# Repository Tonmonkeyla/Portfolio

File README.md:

# Engineering Portfolio

Electrical Engineering student at the University of Canterbury with an interest in embedded systems, RF, aerospace, and power electronics.

## Projects

### GNSS Navigator (STM32 + OpenStreetMaps)
Low-power embedded navigation system built around an STM32 MCU.

- Custom four-layer PCB integrating GNSS, IMU and magnetometer
- C firmware for waypoint navigation and map rendering
- Python tools to compress OpenStreetMap data into binary tiles suitable for MCU storage
- SD card tile streaming based on live NMEA position
- Future revision will incorporate a low-power e-paper display

**Technologies:** STM32, C, Python, KiCad, OpenStreetMaps

---

### Monitor Rotator (ESP32 + BLE)
Wireless monitor orientation sensor powered directly from an HDMI connection.

- Designed a four-layer ESP32 PCB with inertial sensing and BLE
- Developed firmware using ESP-IDF
- Desktop Python application receives orientation data and rotates the display automatically
- Characterised and tuned the integrated 2.4 GHz PCB antenna using a VNA

**Technologies:** ESP32, ESP-IDF, BLE, Python, RF Design

---

### Portable Trailer Light Tester
Battery-powered trailer light tester for automotive diagnostics.

- High-current synchronous buck converter
- Automated lighting test sequences
- Designed for portable operation from an internal battery
- Custom PCB and embedded control firmware

**Technologies:** Power Electronics, Embedded C, KiCad

---

### High-Efficiency LED Array
Custom circular LED lighting module.

- Python-generated PCB layout for uniform LED spacing
- Constant-current buck driver achieving approximately 93% estimated efficiency
- Designed for future integration into IoT lighting systems

**Technologies:** Python, PCB Design, Power Electronics

---

### Artix-7 System-on-Module *(In Progress)*
High-performance FPGA module based on a Xilinx Artix-7.

- Eight-rail power architecture with sequencing
- DDR3 routing and length matching
- Python routing optimisation tools
- High-speed PCB layout

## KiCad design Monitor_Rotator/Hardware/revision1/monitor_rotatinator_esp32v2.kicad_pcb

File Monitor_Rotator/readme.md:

The main idea behind this project was that the internet is becoming increasingly "vertical"; many apps/websites are designed primarily for mobile usage, with desktops being a faint afterthought. 
However, many monitors can be physically rotated, vertically<->horizontally, easily and quickly. The issue lies with manually setting the orientation of the monitor in the operating system; ie. in windows this can only be changed in the display settings. 
Monitors do not "know" what orientation they are in. They simply display images, and do not have the hardware to detect orientation.
A solution to this is to couple an accelerometer to the orientation of the monitor. The easy, and boring, way to do this is to simply attach an externally powered accelerometer board to the monitor (tape).
However this gets messy fast, the power and data cables get tangled with the existing monitor connections, making it a temporary solution at best. 
Powering the accelerometer board directly from the monitor and transmitting the accelerometer data back to the host PC wirelessly solves this, with exactly 0 additional cables.

The complex problem is receiving power from the monitor. While some monitors have USB passthrough and therefore a nice 5V DC supply, most do not. In fact, almost none of the connectors on a standard monitor have any power supply whatsoever, the exception being 500mA DP_PWR 3.3V on DisplayPort inputs.
Unfortunately, most monitors have a single DisplayPort, which is often the main display input. This leaves exactly 0 conventional, viable power supplies. 

HDMI uses a lot of power to receive signals from the host PC (up to ~130 mW). This is largely due to transceiver TMDS terminations being present on the input side, which are directly tied to the exposed connector transceiver pairs. These terminations are implemented as 50 ohm parallel terminations to aVCC, a 3.3v source. A logical zero from the host PC sinks around 10mA of current per termination resistor, which for a typical data pattern (~50% low) is substantial across the 8 terminations available. This effectively means we can sink 5mA*8=~40mA of 3.05V across the 50 ohm terminations, while technically remaining within HDMI design specification. 

This leads to another challenge- how do you consistently sink no greater than 5mA per termination while maximising the available power budget. Connecting the terminations directly to a device side 3.3V net is clearly a bad idea; RF MCUs can draw up to 200mA while transmitting, and even if that were possible within the voltage drop of the terminations it would fry the HDMI aVCC supply instantly. And it isn't possible because it would result in a voltage drop brownout+the catastrophic overcurrent of the HDMI circuit. Initially, my idea was to use a discrete linear current regulator- tie all terminations together through a shunt resistor, V=IR, hold I at 40mA etc. This would use a low VGS PFET in conjunction with a current sense OP-amp to limit the input current to 40mA through to a large capacitor or supercapacitor. Given a (very) low average current draw of the MCU, the voltage of the capacitor net would eventually charge to ~3.3V, which could then be regulated down to an MCU operating voltage of 1.8V or 3V.

The version 2 hardware instead uses a buck converter with op-amp regulated voltage foldback. 6 of the available 8 terminations are used as power terminations, with variable voltage across the termination according to current draw. The remaining 2 are used as reference voltages with minimal current draw; and remain at ~3.3v. The differential voltage between the "reference" and "power" nets is used by the differential op amp to sense average current through the power terminations; and raise the feedback voltage of the buck converter high when input current is exceeded. This effectively uses the 50 ohm terminations themselves as current sense resistors. This current foldback protects the HDMI transceivers from any possible damage.

The power net voltage can approach the reference/VDD "3.3v", so a relatively specialized over the rails OP amp (MCP6021) was required. It was initially designed for the LMV321, however as it turns out the LMV321 does not have rail to rail inputs, as most modern OP-amps have. Additionally the LMV321 has a nasty characteristic when the input differential drops below specification, where the output inverts, effectively dropping the output voltage to the negative rail. As you can imagine buck regulator feedback loops do not tolerate this.

This current regulation feeds into a large (5.7 mF) electrolytic polymer capacitor, which over 100s of mS charges to slightly less than 3.3v. This capacitor net is then regulated to 3.3v exactly using a low quiescent, ultra low input voltage boost converter (TPS61299). This provides stable and low noise power for the MCU, accelerometer, and associated RF circuitry. 

Probing the assembled version 2 revealed that current through the terminations could spike outside of specifications:
A. During startup, when there is significant inrush current into the VIN bulk capacitors of the buck converter.
B. During current spikes on the load side.

The solution to this was to add an additional linear current regulator immediately after the termination nets on the device side. This uses one op-amp unit of a two unit device to control a PFET gate. When the device side termination voltage drops below a set threshold the PFET gate is pulled high to maintain the set current limit, with a very fast response time.

The red trace shows current through R18 into a 2x47uF input bank during startup. Current peaks at 60 mA for a few nanoseconds, before being arrested and maintained at 45 mA until the capacitors are charged and inrush current drops, at which point the switching circuit takes over current regulation. Without the linear regulator it would effectively be 3.3V->50 ohms->ground at startup, drawing ~60 mA (per termination) so 360 mA total through the HDMI transceiver, which would probably fry it.

The "hard" linear current limit and "soft" switching current limit are both user adjustable through potentiometers on the finished board:

This allows for differences in voltage drop through the summing diodes and op-amp differences to be accounted for experimentally.

The MCU chosen was the ESP32C3. In hindsight, this was a poor decision as the BLE power consumption is diminished by sharing circuitry with WIFI. During transmission this can spike to >300 mA at 3.3v, and even in the lowest power, connection maintaining, state still uses ~20 mA on average. This stresses the power budget at best and causes intermittent brownouts when transmissions are not optimized. Eg. to even establish a BLE connection the buffering capacitance needed to be doubled to 11.4 mF. The in-progress version 3 uses a NRF54 series MCU, with less than a tenth of the power consumption, at 1v8.

The version 2 uses a 3216 chip antenna for BLE/WIFI, while the version 2 rev 2 uses a TI AN043 inverted F pcb antenna. 

Surprisingly, both held a stable connection within operating parameters (ie. BLE, within 5 meters) without any tuning, fitting only a 0 ohm as the series element of the PI network. However, the performance was subpar beyond that. As modern RF socs generally adjust the transmission power according to RSSI, it was desirable to increase the antenna efficiency to reduce the power consumption of each packet. 

This required assaying the antenna(s) with a VNA. This was challenging as an RF test port was neglected in both designs. The first attempt was simply soldering a RG316 pigtail to the feedpoint of the antenna:

Unsurprisingly this didn't give a good measurement; with the resonant frequency of the antenna measuring ~1.9 GHz showing that it was significantly detuned by the test fixture:

For the second attempt I instead removed some solder mask, exposing the ground plane into a U.FL-like footprint, then soldered an IPEX-1 connector to it:

This allowed the coaxial shield to be rotated away from the radiating area:

And gave slightly more believable S11, with resonance now measuring around 2.1 GHz:

Which is likely still altered by the large U.FL connector directly adjacent to the radiating area.

Interestingly, rotating the U.FL connector back to parallel with the radiating area detuned the antenna similarly to the pigtail, with S11 resonance dropping back to 1.9 GHz.

Despite the measurements likely still being altered by the U.FL connector, the Smith Chart of the configurating with the coaxial rotated away from the radiating area was used to determine matching component values.

Which, if naively believed, shows that the antenna is very poorly matched with an impedance of 40.7-76.6j ohms at 2.4GHz, and 16.4-35.8j at 2.44Ghz. This suggests a very preliminary matching network on the order of 2-5 nH of series inductance and 1-2 pF of shunt capacitance.

A better takeaway is to always include RF test feedpoints that are sufficiently isolated from the antenna, like a jumper connected U.FL connector (with minimal routed stub) at the opposite end of the transmission line.

### Version 3
Uses STM32WB05 with orders of magnitude lower BLE power consumption over ESP32C3. Larger power budget enables far more robust resistive power supply:

Every TMDS string is individually ORed into a >40F LIC hybrid supercapacitor operating between 3v3 and 2v5, each string is in series with a 100 ohm resistor, current through each termination physically cannot exceed 6 mA, albeit with acceptable resistive losses. 
Individual current limiting resistors makes device compatible with larger range of monitors. Not all monitors power on all transceiver pairs at all times, and some completely power off all transceivers until HPD or source 5V is asserted. Testing shows that when 5V or HPD is asserted a significant subset of monitors raise all transceiver pairs, while some only raise the CLK pair. The power scheme passively handles these cases, and can assert 5V lines through a low quiescent boost 5v net. Low supercapacitor leakage and very low total device current draw (~40 uA) means that the device should be able to operate for ~weeks without any external power at all.   

Dedicated antenna test port/alternate feed through IPX-1 footprint, placed away from antenna on counterbalance side, away from main radiating area. Could use more clearance.

Replaced LTC3406 with better suited TPS62743/RT5707/many clones BGA-8 footprint, quiescent current 350 nA with optimal efficiency in the 10s uA range. Fabrication soon.

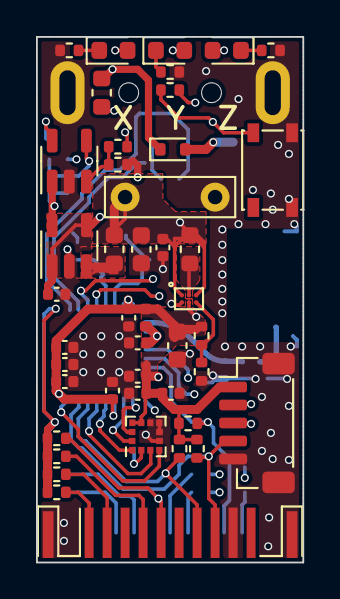
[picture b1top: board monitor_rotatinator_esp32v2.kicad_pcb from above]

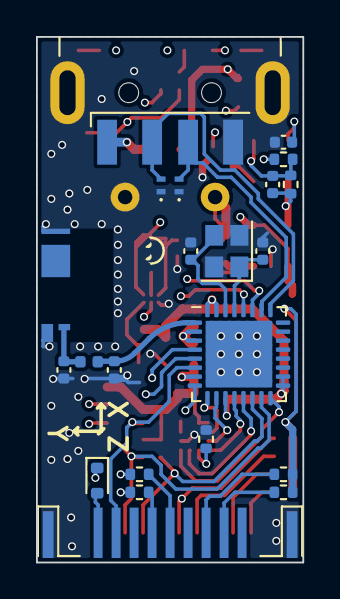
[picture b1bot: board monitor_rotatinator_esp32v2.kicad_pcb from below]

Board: 4 copper layers, 14.8 x 29.2 mm, 65 parts (21 on the bottom side), 46 nets.

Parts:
AE1: Antenna_Chip; RFECA3216060A1T
C1, C10, C20: 4.7uF; C_0402_1005Metric
C3: C_Polarized; C_Rect_L7.0mm_W2.0mm_P5.00mm
C5: 2.2uF; C_0402_1005Metric
C6, C22: 10uF; C_0603_1608Metric
C7, C8: 22pF; C_0402_1005Metric
C9, C11, C13, C16, C17, C18, C19: 100nF; C_0402_1005Metric
C12, C14: TBD; C_0402_1005Metric
C15: 10uF; C_0402_1005Metric
C21: 470p; C_0402_1005Metric
D3, D4, D9: LED; LED_0603_1608Metric
D5, D8: D_Small; D_SOD-523
D6, D7: D_TVS; Texas_DPY0002A_0.6x1mm_P0.65mm
F1: Fuse; Fuse_0603_1608Metric
J1: USB_A; USB_A_CNCTech_1001-011-01101_Horizontal
J2: HDMI_A_1.4; HDMI_A_Contact_Technology_HDMI-19APL2_Horizontal
J3: Conn_01x05_MountingPin; JST_SH_BM05B-SRSS-TB_1x05-1MP_P1.00mm_Vertical
L1: 1uH; L_0603_1608Metric
L2: 2.0nH; L_0402_1005Metric
L3: 0R; L_0402_1005Metric
L4: 2.2uH; L_0603_1608Metric
R5, R6, R16, R17, R18, R19, R20, R21, R22, R23: R_Small; R_0402_1005Metric
R7: DNF; R_0402_1005Metric
R8: 0; R_0402_1005Metric
R9: 100k; R_0402_1005Metric
R10, R14, R26, R29: 10k; R_0402_1005Metric
R11, R12, R13: 330R; R_0402_1005Metric
R27: 6.8k; R_0402_1005Metric
R28: 20k; R_0402_1005Metric
SW1: SW_SPST; SW_SPST_PTS810
U1: LTC3406AES5; TSOT-23-5
U2: WLCSP-6_1.4x1.0mm_P0.4mm
U4: ESP32-C3FH4; QFN-32-1EP_5x5mm_P0.5mm_EP3.7x3.7mm
U5: LIS2DE12; LGA-12_2x2mm_P0.5mm
U6: TSV911xxLx; SOT-23-5
Y1: 40MHz; Crystal_SMD_2520-4Pin_2.5x2.0mm

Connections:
+3V3: C6.1, C9.1, C10.1, C13.1, C15.1, C16.1, C17.1, C18.1, C19.1, J3.1, L2.2, R5.1, R6.1, R7.1, R10.1, R14.1, U2.B2 (VOUT), U4.7 (CHIP_EN), U4.11 (VDD3P3_RTC), U4.17 (VDD3P3_CPU), U4.18 (VDD_SPI), U4.31 (VDDA), U4.32 (VDDA__1), U5.9 (Vdd), U5.10 (Vdd_IO)
ACC_INT1: U4.10 (MTDI), U5.12 (INT1)
ACC_INT2: U4.9 (MTMS), U5.11 (INT2)
ACC_MISO: U4.13 (MTDO), U5.3 (SA0/SDO)
ACC_MOSI: U4.16 (GPIO10), U5.4 (SDA/SDI)
ACC_SCK: U4.12 (MTCK), U5.1 (SCL/SPC)
A_D+: D6.2 (A2), J1.3 (D+), U4.26 (GPIO19)
A_D-: D7.2 (A2), J1.2 (D-), U4.25 (GPIO18)
A_VBUS: D5.2 (A), J1.1 (VBUS)
CK+: J2.10 (CK+), R23.2
CK-: J2.12 (CK-), R22.2
Cap_V+: C3.1, C5.1, C22.1, L1.1, L4.2, U2.A1 (VIN), U2.C1 (EN), U4.4 (XTAL_32K_P)
D0+: J2.7 (D0+), R19.2
D0-: J2.9 (D0-), R18.2, R27.1
D1+: J2.4 (D1+), R20.2
D1-: J2.6 (D1-), R21.2
D2+: J2.1 (D2+), R16.2
D2-: J2.3 (D2-), R17.2
GND: AE1.2 (PCB_Trace), C1.2, C3.2, C5.2, C6.2, C7.1, C8.2, C9.2, C10.2, C11.2, C12.2, C13.2, C14.2, C15.2, C16.2, C17.2, C18.2, C19.2, C20.2, C22.2, D6.1 (A1), D7.1 (A1), J1.4 (GND), J1.5 (Shield), J2.17 (GND), J2.SH, J3.5, J3.MP (MountPin), R8.2, R9.2, R11.2, R12.2, R13.2, R28.2, SW1.1 (A), U1.2 (GND), U2.A2 (GND), U4.33 (GND), U5.5 (RES), U5.6 (GND), U5.7 (GND), U5.8 (GND), U6.2 (V-), Y1.2, Y1.4
GPIO2: J2.16 (SDA), R6.2, U4.6 (GPIO2)
GPIO8: J2.13 (CEC), R5.2, U4.14 (GPIO8)
GPIO9: J2.15 (SCL), J3.4, R10.2, U4.15 (GPIO9)
unnamed: AE1.1 (FEED), C14.1, L3.2
unnamed: D3.1 (K), R11.1
unnamed: D4.1 (K), R12.1
unnamed: D8.2 (A), J2.18 (+5V)
unnamed: D9.1 (K), R13.1
unnamed: R23.1, R26.2
unnamed: C20.1, F1.1, U1.1 (RUN), U1.4 (VIN)
unnamed: L4.1, U1.3 (SW)
unnamed: C21.2, R29.2, U1.5 (VOUT), U6.1
unnamed: L1.2, U2.B1 (SW)
unnamed: R7.2, R8.1, U2.C2 (VSEL)
unnamed: C12.1, L3.1, U4.1 (LNA_IN)
unnamed: C11.1, L2.1, U4.2 (VDD3P3), U4.3 (VDD3P3__1)
unnamed: C7.2, U4.29 (XTAL_N), Y1.1
unnamed: C8.1, U4.30 (XTAL_P), Y1.3
unnamed: R9.1, U5.2 (~CS)
unnamed: R26.1, R28.1, U6.3 (+)
unnamed: C21.1, R27.2, R29.1, U6.4 (-)
unnamed: C1.1, R22.1, U6.5 (V+)
RXD: D3.2 (A), J3.3, U4.27 (U0RXD)
TXD: D4.2 (A), J3.2, U4.28 (U0TXD)
User_LED3: D9.2 (A), U4.8 (GPIO3)
User_SW1: R14.2, SW1.2 (B), U4.5 (XTAL_32K_N)
VBUS: D5.1 (K), D8.1 (K), F1.2, R16.1, R17.1, R18.1, R19.1, R20.1, R21.1

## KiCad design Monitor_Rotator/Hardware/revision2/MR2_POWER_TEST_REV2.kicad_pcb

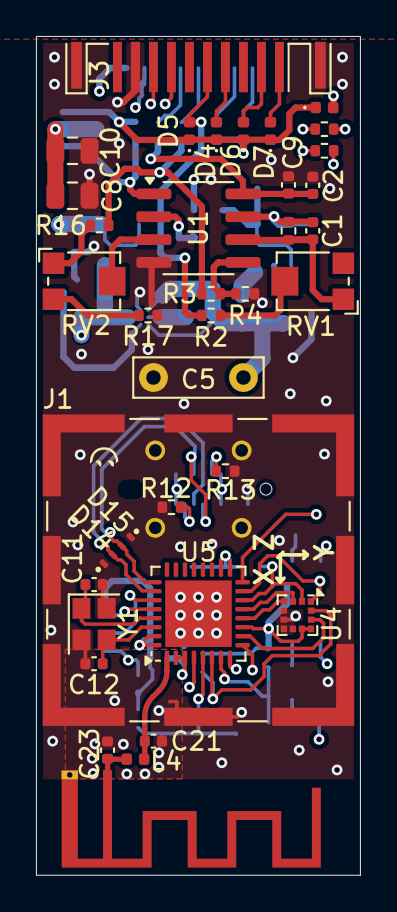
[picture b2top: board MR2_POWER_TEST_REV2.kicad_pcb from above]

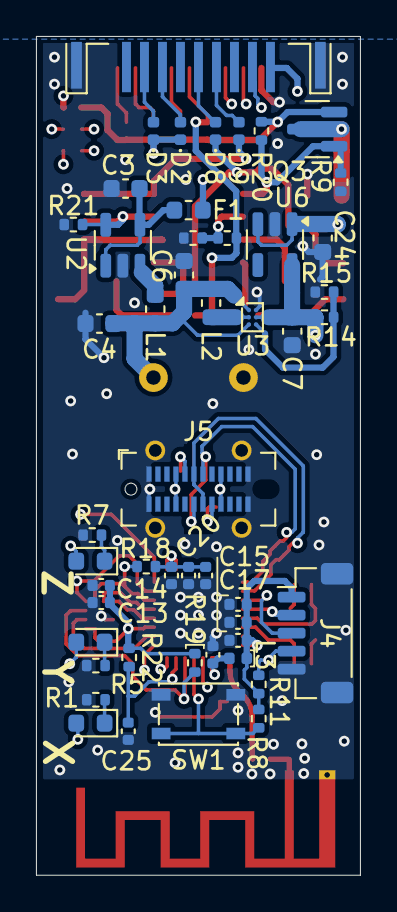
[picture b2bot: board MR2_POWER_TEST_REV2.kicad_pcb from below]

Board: 4 copper layers, 18.0 x 46.6 mm, 85 parts (48 on the bottom side), 57 nets.

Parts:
AE1: Antenna_Chip; Texas_SWRA117D_2.4GHz_Left
C1: 470p; C_0402_1005Metric
C2, C9: 100n; C_0402_1005Metric
C3: 4.7uF; C_0603_1608Metric
C4: 10uF; C_0603_1608Metric
C5: C_Polarized; C_Rect_L7.0mm_W2.0mm_P5.00mm
C6, C7: 22uF; C_0603_1608Metric
C8, C10: 47uF; C_0805_2012Metric
C11, C12: 22pF; C_0402_1005Metric
C13, C16, C17, C18, C19, C20, C22, C25: 100nF; C_0402_1005Metric
C14: 4.7uF; C_0402_1005Metric
C15: 10uF; C_0402_1005Metric
C21, C23: TBD; C_0402_1005Metric
C24: 2.2uF; C_0603_1608Metric
D2, D3, D4, D5, D6, D7, D8, D9, D16: D_Small; D_0402_1005Metric
D10, D11, D12: LED; LED_0603_1608Metric
D14, D15: D_TVS; Texas_DPY0002A_0.6x1mm_P0.65mm
F1: 200mA; Fuse_0603_1608Metric
J1: RFShield_OnePiece; Laird_Technologies_BMI-S-102_16.50x16.50mm
J3: HDMI_A_1.4; HDMI_A_Contact_Technology_HDMI-19APL2_Horizontal
J4: Conn_01x05_MountingPin; JST_SH_BM05B-SRSS-TB_1x05-1MP_P1.00mm_Vertical
J5: USB_C_Receptacle; USB_C_Receptacle_GCT_USB4115-03-C
L1: 2.2uH; L_0603_1608Metric
L2: 1uH; L_0603_1608Metric
L3: 2.0nH; L_0402_1005Metric
L4: 0R; L_0402_1005Metric
Q3: Q_PMOS_GSD; SOT-23
R1, R5, R7: 1.2k; R_0402_1005Metric
R2, R4, R6, R9, R11, R21: 100k; R_0402_1005Metric
R3: 120k; R_0402_1005Metric
R8, R18, R19, R20, R22, R23, R24: 10k; R_0402_1005Metric
R10, R17, R25: 200k; R_0402_1005Metric
R12, R13: 5.1k; R_0402_1005Metric
R14: DNF; R_0402_1005Metric
R15: 0; R_0402_1005Metric
R16: 50k; R_0402_1005Metric
RV1, RV2: 100k; Potentiometer_Bourns_TC33X_Vertical
SW1: SW_SPST; SW_SPST_PTS810
U1: LMV358; SOIC-8_3.9x4.9mm_P1.27mm
U2: LTC3406AES5; TSOT-23-5
U3: WLCSP-6_1.4x1.0mm_P0.4mm
U4: LIS2DE12; LGA-12_2x2mm_P0.5mm
U5: ESP32-C3FH4; QFN-32-1EP_5x5mm_P0.5mm_EP3.7x3.7mm
U6: AP2112K-3.3; SOT-23-5
Y1: 40MHz; Crystal_SMD_2520-4Pin_2.5x2.0mm

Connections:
+3V3: C7.1, C13.1, C14.1, C15.1, C17.1, C18.1, C19.1, C20.1, C22.1, J4.1, L3.2, R8.1, R11.1, R14.1, R18.1, R19.1, R22.1, U3.B2 (VOUT), U4.9 (Vdd), U4.10 (Vdd_IO), U5.11 (VDD3P3_RTC), U5.17 (VDD3P3_CPU), U5.18 (VDD_SPI), U5.31 (VDDA), U5.32 (VDDA__1), U6.5 (VOUT)
+5V: C24.1, J5.A4 (VBUS), J5.A9 (VBUS), J5.B4 (VBUS), J5.B9 (VBUS), U6.1 (VIN), U6.3 (EN)
ACC_INT1: R24.1, U5.9 (MTMS)
ACC_INT2: U4.11 (INT2), U5.10 (MTDI)
ACC_MISO: U4.3 (SA0/SDO), U5.13 (MTDO)
ACC_MOSI: U4.4 (SDA/SDI), U5.12 (MTCK)
ACC_SCK: J3.13 (CEC), U5.16 (GPIO10)
A_D+: D14.2 (A2), J5.A6 (D+), J5.B6 (D+), U5.26 (GPIO19)
A_D-: D15.2 (A2), J5.A7 (D-), J5.B7 (D-), U5.25 (GPIO18)
CK+: D8.2 (A), J3.10 (CK+)
CK-: D9.2 (A), J3.12 (CK-)
Cap_V+: C4.1, C5.1, C6.1, L1.2, L2.1, U3.A1 (VIN), U3.C1 (EN), U5.4 (XTAL_32K_P)
D0+: D4.2 (A), J3.7 (D0+)
D0-: D5.2 (A), J3.9 (D0-), R2.1, R10.2
D1+: D3.2 (A), J3.4 (D1+)
D1-: D2.2 (A), J3.6 (D1-)
D2+: D7.2 (A), J3.1 (D2+)
D2-: D6.2 (A), J3.3 (D2-)
GND: AE1.2 (PCB_Trace), C2.1, C3.2, C4.2, C5.2, C6.2, C7.2, C8.1, C9.1, C10.1, C11.1, C12.2, C13.2, C14.2, C15.2, C16.2, C17.2, C18.2, C19.2, C20.2, C21.2, C22.2, C23.2, C24.2, C25.2, D14.1 (A1), D15.1 (A1), J1.1 (Shield), J3.17 (GND), J3.SH, J4.5, J4.MP (MountPin), J5.A1 (GND), J5.A12 (GND), J5.B1 (GND), J5.B12 (GND), J5.S1 (SHIELD), R1.2, R4.2, R5.2, R7.2, R9.2, R12.2, R13.2, R15.2, R17.2, R21.2, R25.1, SW1.1 (A), U1.4 (V-), U2.2 (GND), U3.A2 (GND), U4.5 (RES), U4.6 (GND), U4.7 (GND), U4.8 (GND), U5.33 (GND), U6.2 (GND), Y1.2, Y1.4
GPIO2: R19.2, U4.12 (INT1), U5.6 (GPIO2)
GPIO8: R18.2, U4.2 (~CS), U5.14 (GPIO8)
GPIO9: J4.4, R11.2, U4.1 (SCL/SPC), U5.15 (GPIO9)
unnamed: AE1.1 (FEED), C23.1, L4.2
unnamed: D8.1 (K), R3.2, R16.1
unnamed: C2.2, C9.2, D9.1 (K), U1.8 (V+)
unnamed: D10.1 (K), R1.1
unnamed: D11.1 (K), R5.1
unnamed: D12.1 (K), R7.1
unnamed: D16.2 (A), J3.18 (+5V)
unnamed: J3.15 (SCL), R23.2
unnamed: J3.16 (SDA), R24.2
unnamed: J5.A5 (CC1), R13.1
unnamed: J5.B5 (CC2), R12.1
unnamed: R2.2, RV1.2
unnamed: R16.2, RV2.1
unnamed: R17.1, RV2.3
unnamed: RV2.2, U1.3 (+)
unnamed: R10.1, R25.2, U1.2 (-)
unnamed: R3.1, R4.1, U1.5 (+)
unnamed: C1.1, R6.1, RV1.1, U1.6 (-)
unnamed: C3.1, F1.1, U2.1 (RUN), U2.4 (VIN)
unnamed: L1.1, U2.3 (SW)
unnamed: C1.2, R6.2, R21.1, U1.7, U2.5 (VOUT)
unnamed: L2.2, U3.B1 (SW)
unnamed: R14.2, R15.1, U3.C2 (VSEL)
unnamed: C25.1, R22.2, U5.7 (CHIP_EN)
unnamed: C21.1, L4.1, U5.1 (LNA_IN)
unnamed: C16.1, L3.1, U5.2 (VDD3P3), U5.3 (VDD3P3__1)
unnamed: C11.2, U5.29 (XTAL_N), Y1.1
unnamed: C12.1, U5.30 (XTAL_P), Y1.3
RXD: D10.2 (A), J4.3, U5.27 (U0RXD)
TXD: D11.2 (A), J4.2, U5.28 (U0TXD)
User_LED3: D12.2 (A), R23.1, U5.8 (GPIO3)
User_SW1: R8.2, SW1.2 (B), U5.5 (XTAL_32K_N)
VBUS: D2.1 (K), D3.1 (K), D4.1 (K), D5.1 (K), D6.1 (K), D7.1 (K), D16.1 (K), Q3.2 (S), R20.2
VDD: C8.2, C10.2, F1.2, Q3.3 (D)
lin_reg: Q3.1 (G), R9.1, R20.1, U1.1

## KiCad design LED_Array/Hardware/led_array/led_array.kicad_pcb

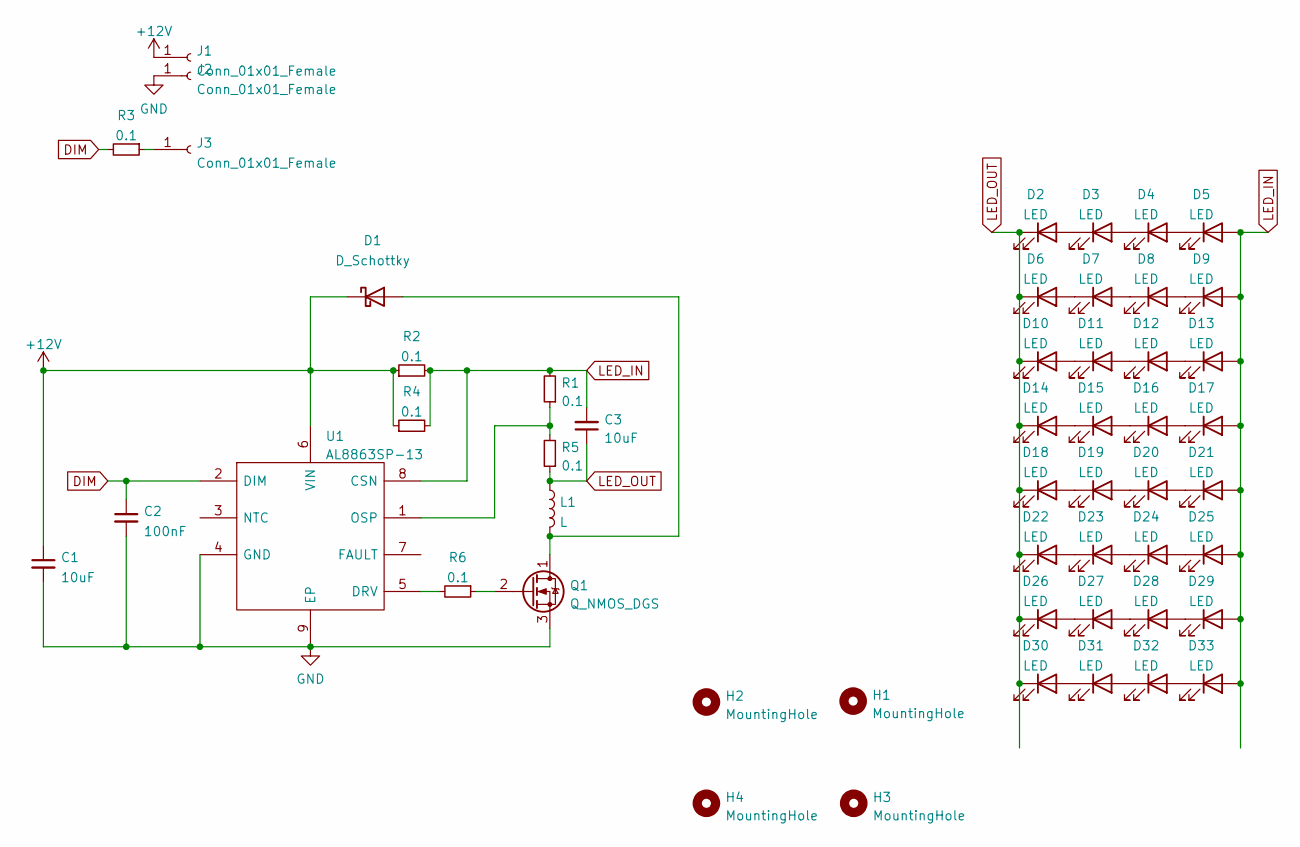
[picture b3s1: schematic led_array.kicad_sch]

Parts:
C1, C3: 10uF; C_1206_3216Metric
C2: 100nF; C_0402_1005Metric
D1: D_Schottky; D_SMA
D2, D3, D4, D5, D6, D7, D8, D9, D10, D11, D12, D13, D14, D15, D16, D17, D18, D19, D20, D21, D22, D23, D24, D25, D26, D27, D28, D29, D30, D31, D32, D33: LED; LM301B
H1, H2, H3, H4: MountingHole; MountingHole_3.2mm_M3
J1, J2, J3: Conn_01x01_Female; POKE-HOME
L1: L; L_Bourns-SRN8040_8x8.15mm
Q1: Q_NMOS_DGS; VSONP-8-1EP_5x6_P1.27mm
R1, R6: 0.1; R_0402_1005Metric
R2, R4: 0.1; R_1206_3216Metric
R3, R5: 0.1; R_0805_2012Metric
U1: AL8863SP-13; SOIC127P600X170-9N; Mouser Part Number 621-AL8863SP-13

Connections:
+12V: C1.1, D1.1 (K), J1.1, R2.1, R4.1, U1.6 (VIN)
DIM: C2.1, R3.2, U1.2 (DIM)
GND: C1.2, C2.2, J2.1, Q1.3 (S), U1.4 (GND), U1.9 (EP)
LED_IN: C3.2, D5.2 (A), D9.2 (A), D13.2 (A), D17.2 (A), D21.2 (A), D25.2 (A), D29.2 (A), D33.2 (A), R1.2, R2.2, R4.2, U1.8 (CSN)
LED_OUT: C3.1, D2.1 (K), D6.1 (K), D10.1 (K), D14.1 (K), D18.1 (K), D22.1 (K), D26.1 (K), D30.1 (K), L1.1, R5.1
unnamed: D1.2 (A), L1.2, Q1.1 (D)
unnamed: D2.2 (A), D3.1 (K)
unnamed: D3.2 (A), D4.1 (K)
unnamed: D4.2 (A), D5.1 (K)
unnamed: D6.2 (A), D7.1 (K)
unnamed: D7.2 (A), D8.1 (K)
unnamed: D8.2 (A), D9.1 (K)
unnamed: D10.2 (A), D11.1 (K)
unnamed: D11.2 (A), D12.1 (K)
unnamed: D12.2 (A), D13.1 (K)
unnamed: D14.2 (A), D15.1 (K)
unnamed: D15.2 (A), D16.1 (K)
unnamed: D16.2 (A), D17.1 (K)
unnamed: D18.2 (A), D19.1 (K)
unnamed: D19.2 (A), D20.1 (K)
unnamed: D20.2 (A), D21.1 (K)
unnamed: D22.2 (A), D23.1 (K)
unnamed: D23.2 (A), D24.1 (K)
unnamed: D24.2 (A), D25.1 (K)
unnamed: D26.2 (A), D27.1 (K)
unnamed: D27.2 (A), D28.1 (K)
unnamed: D28.2 (A), D29.1 (K)
unnamed: D30.2 (A), D31.1 (K)
unnamed: D31.2 (A), D32.1 (K)
unnamed: D32.2 (A), D33.1 (K)
unnamed: J3.1, R3.1
unnamed: Q1.2 (G), R6.1
unnamed: R1.1, R5.2, U1.1 (OSP)
unnamed: R6.2, U1.5 (DRV)

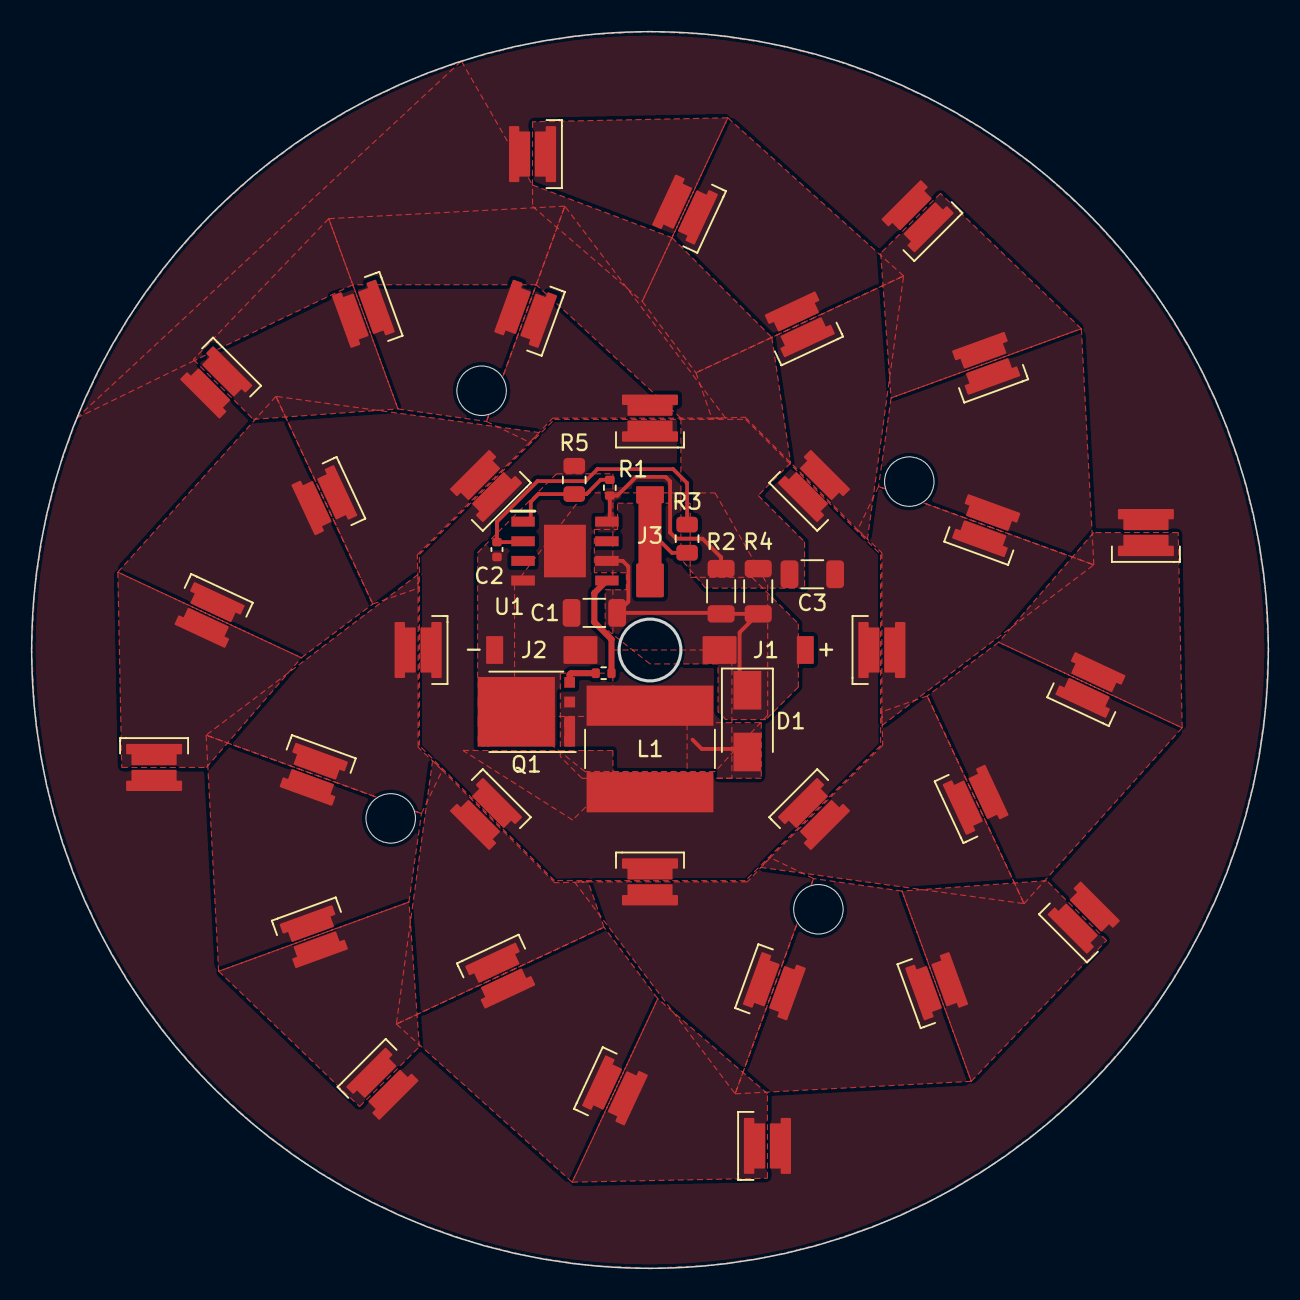
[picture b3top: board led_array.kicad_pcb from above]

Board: 2 copper layers, 80.0 x 80.0 mm, 52 parts (0 on the bottom side), 34 nets.

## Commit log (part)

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2025-07-15 Add files via upload
    initial commit
2025-07-15 Create README.md
    Added brief readme
2025-07-16 Update gatts_table_creat_demo.c
    fixes
2025-07-18 Add files via upload
    added images/demo
